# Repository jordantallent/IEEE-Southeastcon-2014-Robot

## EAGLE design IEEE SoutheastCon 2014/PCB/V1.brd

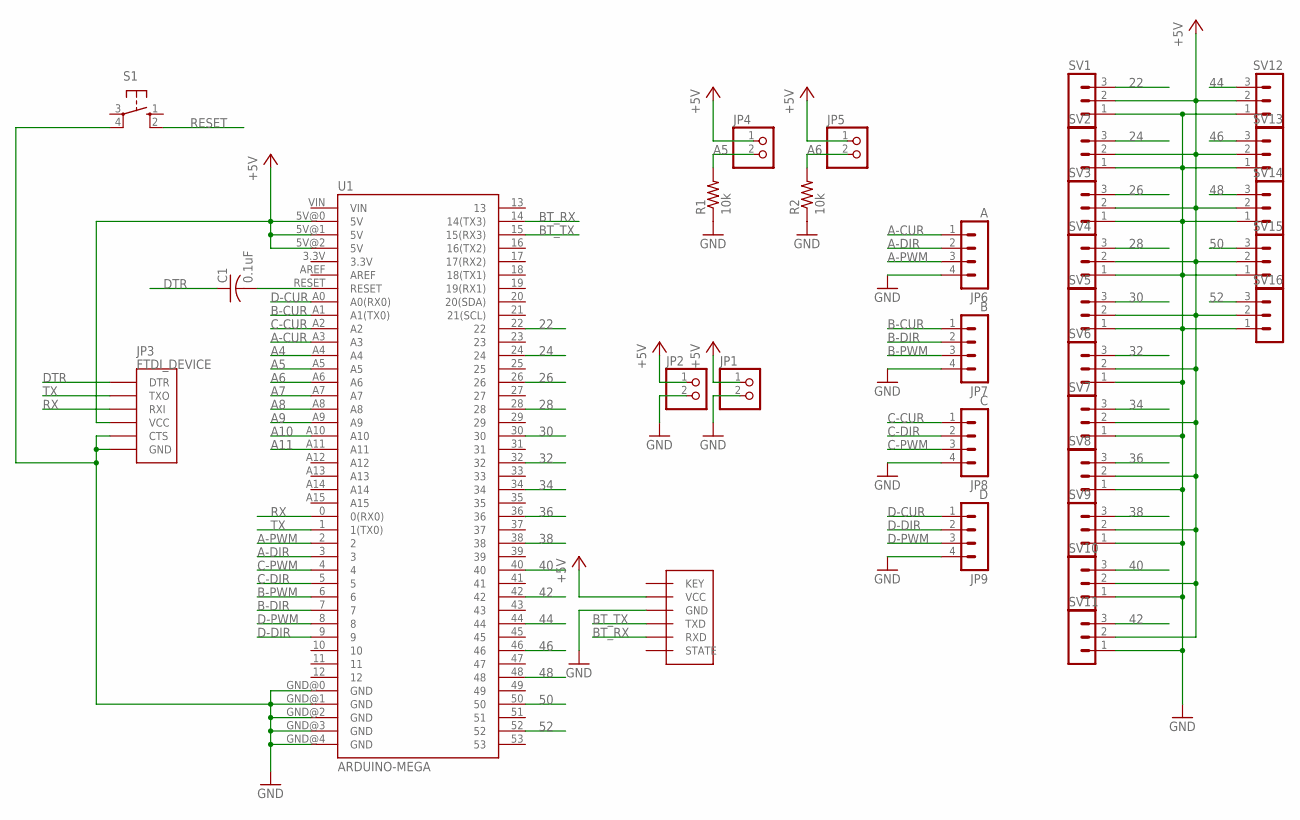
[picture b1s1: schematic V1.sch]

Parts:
BT1: BT_MODULEVERTICAL; BT_MODULE_V
C1: 0.1uF; C025-024X044
JP1, JP2, JP4, JP5: PINHD-1X2; 1X02
JP3: FTDI_DEVICE; FTDI_DEVICE_SIDE
JP6: A; MA04-1
JP7: B; MA04-1
JP8: C; MA04-1
JP9: D; MA04-1
R1, R2: 10k; 0204/7
S1: 10-XX; B3F-10XX
SV1, SV2, SV3, SV4, SV5, SV6, SV7, SV8, SV9, SV10, SV11, SV12, SV13, SV14, SV15, SV16: MA03-1
U1: ARDUINO-MEGA; ARDUINO_MEGA_PINS_ONLY

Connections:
22: SV1.3, U1.22
24: SV2.3, U1.24
26: SV3.3, U1.26
28: SV4.3, U1.28
30: SV5.3, U1.30
32: SV6.3, U1.32
34: SV7.3, U1.34
36: SV8.3, U1.36
38: SV9.3, U1.38
40: SV10.3, U1.40
42: SV11.3, U1.42
44: SV12.3, U1.44
46: SV13.3, U1.46
48: SV14.3, U1.48
50: SV15.3, U1.50
52: SV16.3, U1.52
+5V: BT1.VCC, JP1.1, JP2.1, JP3.P$4 (VCC), JP4.1, JP5.1, SV1.2, SV2.2, SV3.2, SV4.2, SV5.2, SV6.2, SV7.2, SV8.2, SV9.2, SV10.2, SV11.2, SV12.2, SV13.2, SV14.2, SV15.2, SV16.2, U1.5V@0 (5V), U1.5V@1 (5V), U1.5V@2 (5V)
A4: U1.A4
A5: JP4.2, R1.2, U1.A5
A6: JP5.2, R2.2, U1.A6
A7: U1.A7
A8: U1.A8
A9: U1.A9
A10: U1.A10
A11: U1.A11
A-CUR: JP6.1, U1.A3
A-DIR: JP6.2, U1.3
A-PWM: JP6.3, U1.2
B-CUR: JP7.1, U1.A1 (A1(TX0))
B-DIR: JP7.2, U1.7
B-PWM: JP7.3, U1.6
BT_RX: BT1.RXD, U1.14 (14(TX3))
BT_TX: BT1.TXD, U1.15 (15(RX3))
C-CUR: JP8.1, U1.A2
C-DIR: JP8.2, U1.5
C-PWM: JP8.3, U1.4
D-CUR: JP9.1, U1.A0 (A0(RX0))
D-DIR: JP9.2, U1.9
D-PWM: JP9.3, U1.8
DTR: C1.1, JP3.P$1 (DTR)
GND: BT1.GND, JP1.2, JP2.2, JP3.P$5 (CTS), JP3.P$6 (GND), JP6.4, JP7.4, JP8.4, JP9.4, R1.1, R2.1, S1.4 (P1), SV1.1, SV2.1, SV3.1, SV4.1, SV5.1, SV6.1, SV7.1, SV8.1, SV9.1, SV10.1, SV11.1, SV12.1, SV13.1, SV14.1, SV15.1, SV16.1, U1.GND@0 (GND), U1.GND@1 (GND), U1.GND@2 (GND), U1.GND@3 (GND), U1.GND@4 (GND)
RESET: C1.2, S1.2 (S1), U1.RESET
RX: JP3.P$3 (RXI), U1.0 (0(RX0))
TX: JP3.P$2 (TXO), U1.1 (1(TX0))

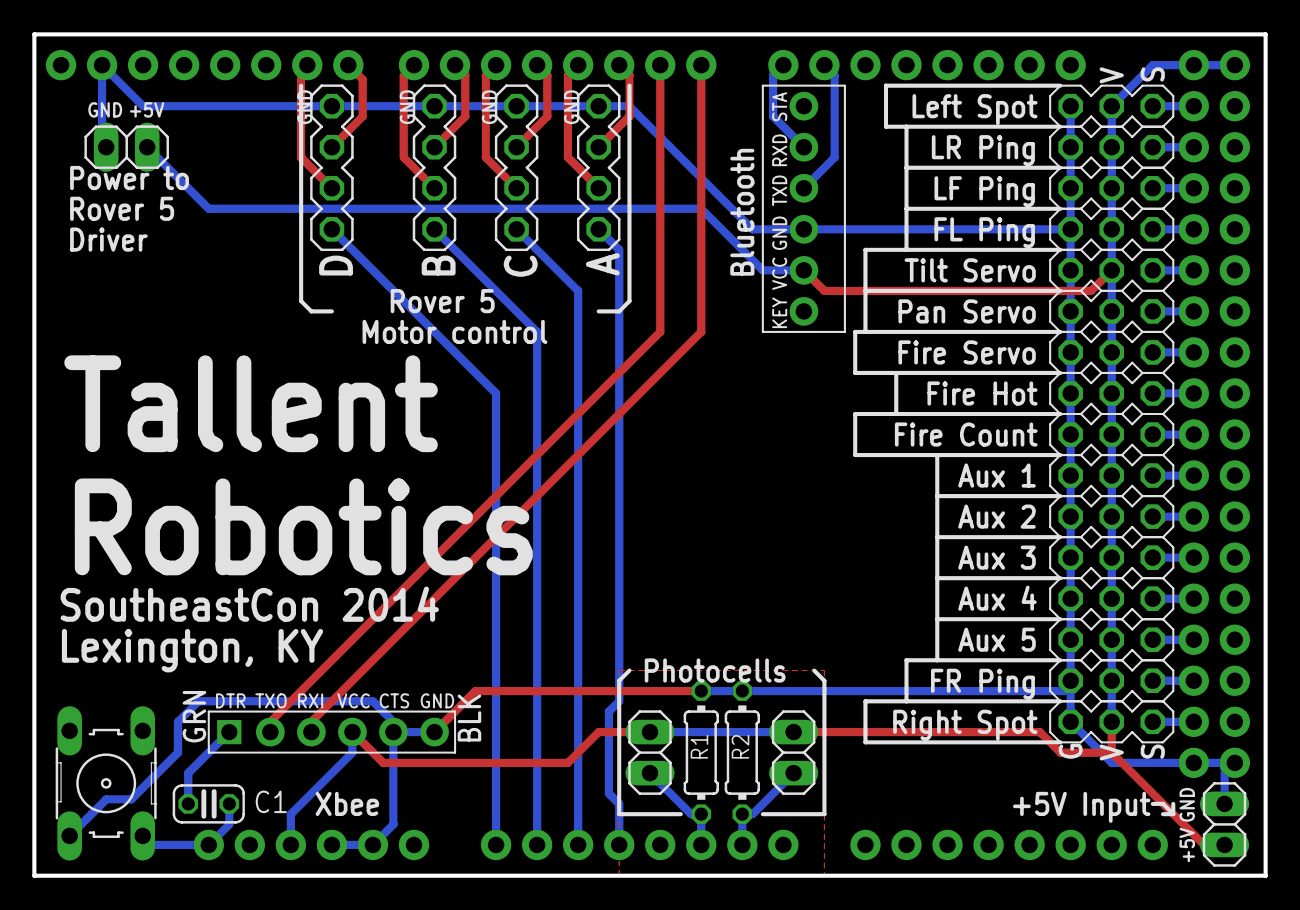
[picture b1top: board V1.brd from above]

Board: 2 copper layers, 76.2 x 52.1 mm, 31 parts (0 on the bottom side), 38 nets.

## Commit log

2015-08-30 All files
    These are all of my files from the project.

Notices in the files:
parts and their libraries:
SparkFun-Boards: Licensing: CC v3.0 Share-Alike You are welcome to use this library for commercial purposes.
